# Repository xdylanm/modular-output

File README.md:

# Output Module

An audio output module for Eurorack, combining two mono input channels into a stereo output with a panning mixer. The stereo output is suitable to drive headphones or small speakers.

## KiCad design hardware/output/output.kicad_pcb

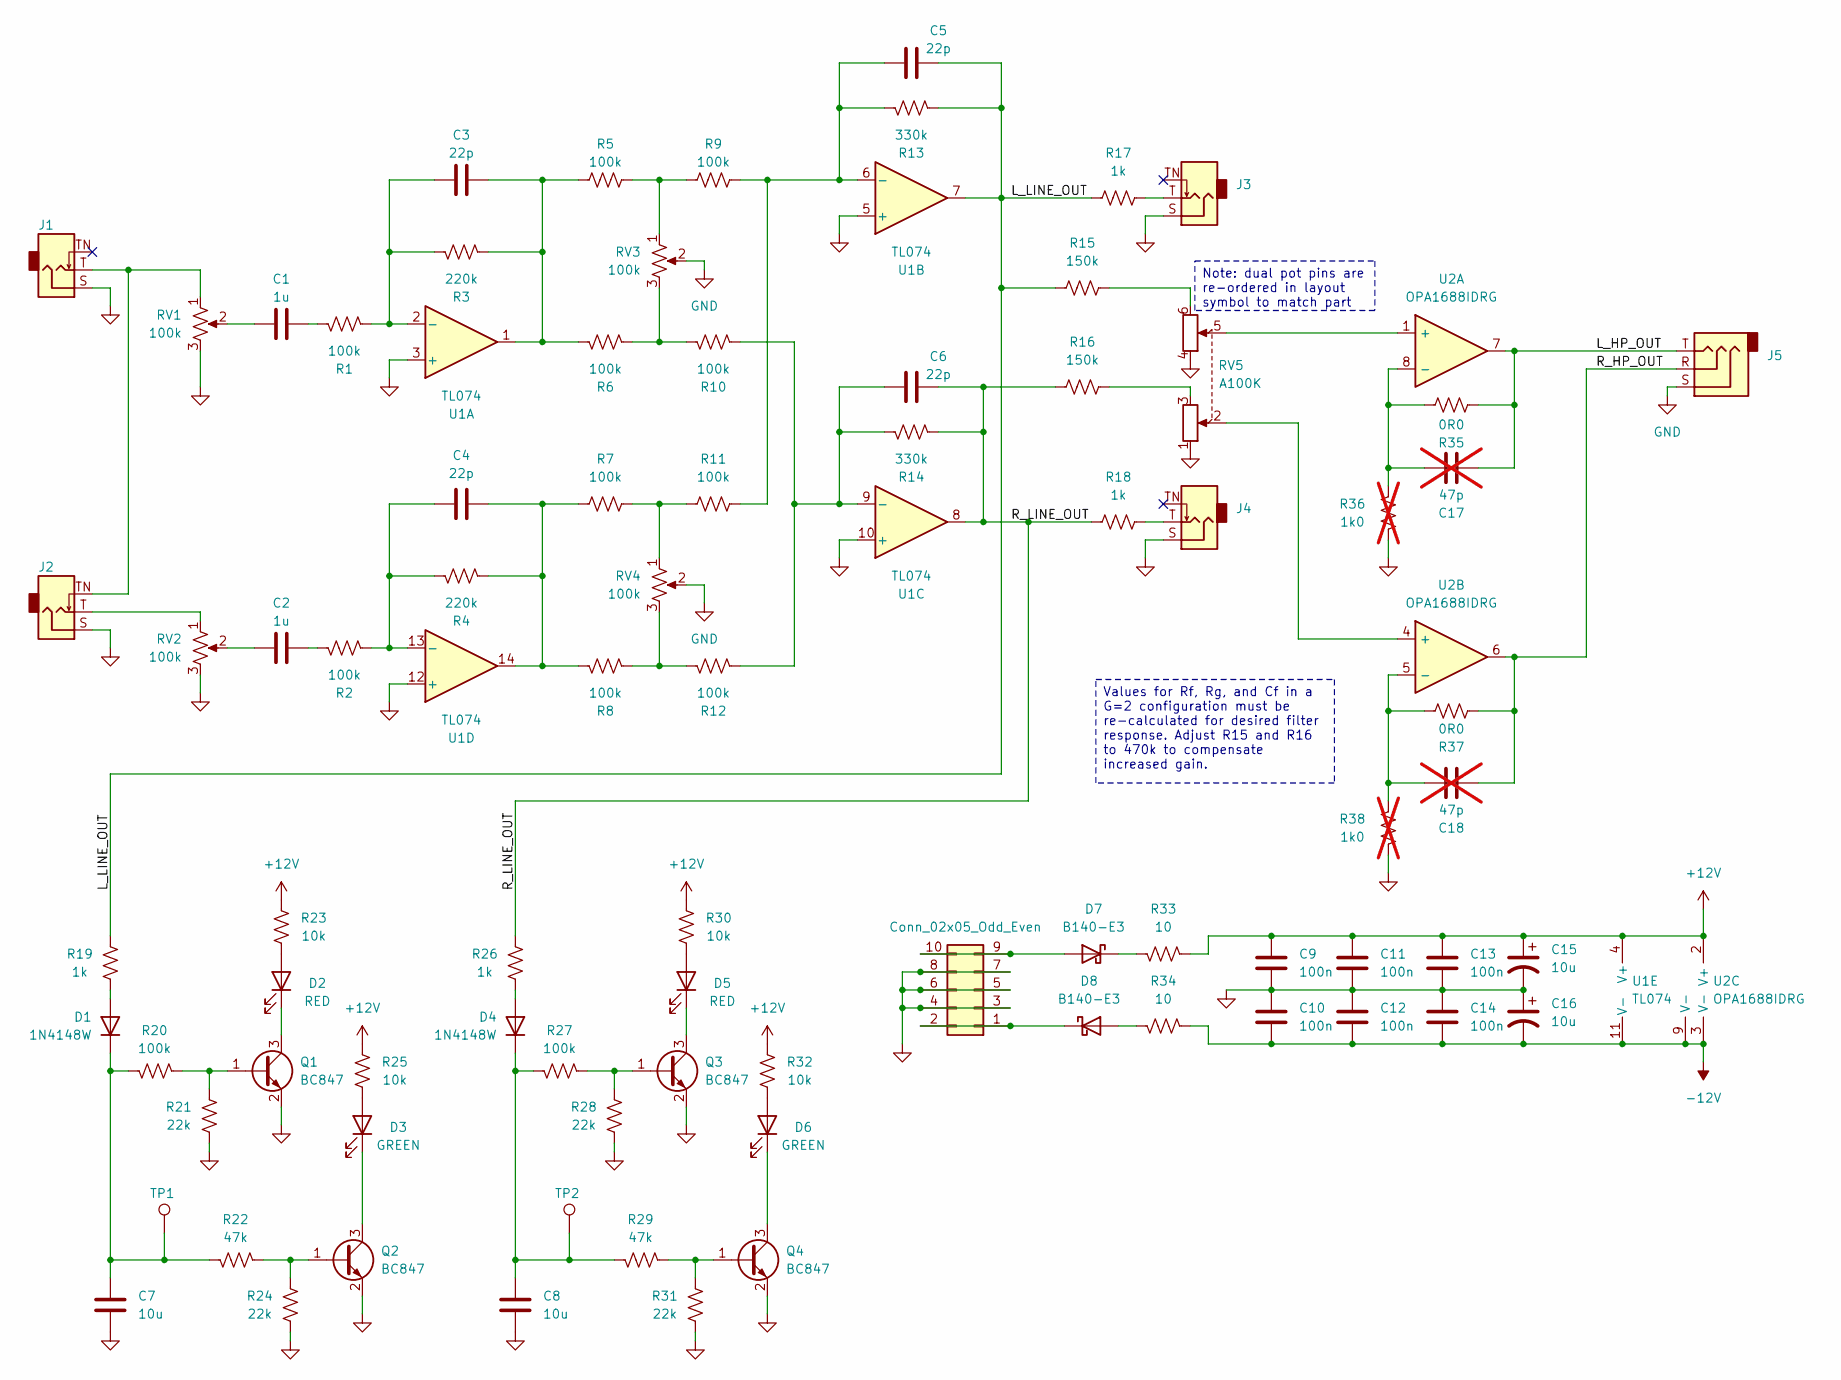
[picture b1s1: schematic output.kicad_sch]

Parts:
C1, C2: 1u; C_0805_2012Metric_Pad1.18x1.45mm_HandSolder
C3, C4, C5, C6: 22p; C_0805_2012Metric_Pad1.18x1.45mm_HandSolder
C7, C8: 10u; C_0805_2012Metric_Pad1.18x1.45mm_HandSolder
C9, C10, C11, C12, C13, C14: 100n; C_0805_2012Metric_Pad1.18x1.45mm_HandSolder
C15, C16: 10u; CP_Radial_D5.0mm_P2.00mm
C17, C18: 47p; C_0805_2012Metric_Pad1.18x1.45mm_HandSolder; not fitted
D1, D4: 1N4148W; D_SOD-123
D2, D5: RED; LED_D3.0mm_Clear
D3, D6: GREEN; LED_D3.0mm_Clear
D7, D8: B140-E3; D_SMA
J1, J2, J3, J4: AudioJack2_SwitchT; Jack_3.5mm_QingPu_WQP-PJ301M-12_Vertical_Slim
J5: AudioJack3; Jack_3.5mm_QingPu_WQP-PJ301CM_Vertical
J6: Conn_02x05_Odd_Even; IDC-Header_2x05_P2.54mm_Vertical
Q1, Q2, Q3, Q4: BC847; SOT-23
R1, R2, R5, R6, R7, R8, R9, R10, R11, R12, R20, R27: 100k; R_0805_2012Metric_Pad1.20x1.40mm_HandSolder
R3, R4: 220k; R_0805_2012Metric_Pad1.20x1.40mm_HandSolder
R13, R14: 330k; R_0805_2012Metric_Pad1.20x1.40mm_HandSolder
R15, R16: 150k; R_0805_2012Metric_Pad1.20x1.40mm_HandSolder
R17, R18, R19, R26: 1k; R_0805_2012Metric_Pad1.20x1.40mm_HandSolder
R21, R24, R28, R31: 22k; R_0805_2012Metric_Pad1.20x1.40mm_HandSolder
R22, R29: 47k; R_0805_2012Metric_Pad1.20x1.40mm_HandSolder
R23, R25, R30, R32: 10k; R_0805_2012Metric_Pad1.20x1.40mm_HandSolder
R33, R34: 10; R_0805_2012Metric_Pad1.20x1.40mm_HandSolder
R35, R37: 0R0; R_0805_2012Metric_Pad1.20x1.40mm_HandSolder
R36, R38: 1k0; R_0805_2012Metric_Pad1.20x1.40mm_HandSolder; not fitted
RV1, RV2, RV3, RV4: 100k; Potentiometer_Bourns_PTV09A-1_Single_Vertical
RV5: A100K; Potentiometer_Bourns_PTV112-4_Dual_Vertical
TP1, TP2: TestPoint; TestPoint_Pad_D1.5mm
U1: TL074; SOIC-14_3.9x8.7mm_P1.27mm
U2: OPA1688IDRG; WSON-8-1EP_3x3mm_P0.5mm_EP1.2x2mm

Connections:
+12V: C9.2, C11.2, C13.2, C15.1, R23.1, R25.1, R30.1, R32.1, R33.1, U1.4 (V+), U2.2 (V+)
-12V: C10.1, C12.1, C14.1, C16.2, R34.1, U1.11 (V-), U2.3 (V-), U2.9 (V-)
/L_HP_OUT: C17.2, J5.T, R35.1, U2.7
/L_LINE_OUT: C5.2, R13.2, R15.1, R17.1, R19.2, U1.7
/R_HP_OUT: C18.2, J5.R, R37.1, U2.6
/R_LINE_OUT: C6.2, R14.2, R16.1, R18.1, R26.2, U1.8
GND: C7.1, C8.1, C9.1, C10.2, C11.1, C12.2, C13.1, C14.2, C15.2, C16.1, J1.S, J2.S, J3.S, J4.S, J5.S, J6.3, J6.4, J6.5, J6.6, J6.7, J6.8, Q1.2 (E), Q2.2 (E), Q3.2 (E), Q4.2 (E), R21.1, R24.1, R28.1, R31.1, R36.2, R38.2, RV1.3, RV2.3, RV3.2, RV4.2, RV5.1, RV5.4, RV5.SH, U1.3 (+), U1.5 (+), U1.10 (+), U1.12 (+)
unnamed: C1.1, RV1.2
unnamed: C1.2, R1.1
unnamed: C2.1, RV2.2
unnamed: C2.2, R2.1
unnamed: C3.2, R3.2, R5.1, R6.1, U1.1
unnamed: C4.2, R4.2, R7.1, R8.1, U1.14
unnamed: D1.2 (A), R19.1
unnamed: C7.2, D1.1 (K), R20.2, R22.2, TP1.1
unnamed: D2.2 (A), R23.2
unnamed: D2.1 (K), Q1.3 (C)
unnamed: D3.2 (A), R25.2
unnamed: D3.1 (K), Q2.3 (C)
unnamed: D4.2 (A), R26.1
unnamed: C8.2, D4.1 (K), R27.2, R29.2, TP2.1
unnamed: D5.2 (A), R30.2
unnamed: D5.1 (K), Q3.3 (C)
unnamed: D6.2 (A), R32.2
unnamed: D6.1 (K), Q4.3 (C)
unnamed: D7.2 (A), J6.9, J6.10
unnamed: D7.1 (K), R33.2
unnamed: D8.2 (A), R34.2
unnamed: D8.1 (K), J6.1, J6.2
unnamed: J1.T, J2.TN, RV1.1
unnamed: J2.T, RV2.1
unnamed: J3.T, R17.2
unnamed: J4.T, R18.2
unnamed: Q1.1 (B), R20.1, R21.2
unnamed: Q2.1 (B), R22.1, R24.2
unnamed: Q3.1 (B), R27.1, R28.2
unnamed: Q4.1 (B), R29.1, R31.2
unnamed: R5.2, R9.1, RV3.1
unnamed: R6.2, R10.1, RV3.3
unnamed: R7.2, R11.1, RV4.1
unnamed: R8.2, R12.1, RV4.3
unnamed: R15.2, RV5.6
unnamed: R16.2, RV5.3
unnamed: C3.1, R1.2, R3.1, U1.2 (-)
unnamed: C5.1, R9.2, R11.2, R13.1, U1.6 (-)
unnamed: C6.1, R10.2, R12.2, R14.1, U1.9 (-)
unnamed: C4.1, R2.2, R4.1, U1.13 (-)
unnamed: RV5.5, U2.1 (+)
unnamed: C17.1, R35.2, R36.1, U2.8 (-)
unnamed: RV5.2, U2.4 (+)
unnamed: C18.1, R37.2, R38.1, U2.5 (-)

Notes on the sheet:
Note: dual pot pins are re-ordered in layout symbol to match part
Values for Rf, Rg, and Cf in a G=2 configuration must be re-calculated for desired filter response. Adjust R15 and R16 to 470k to compensate increased gain.

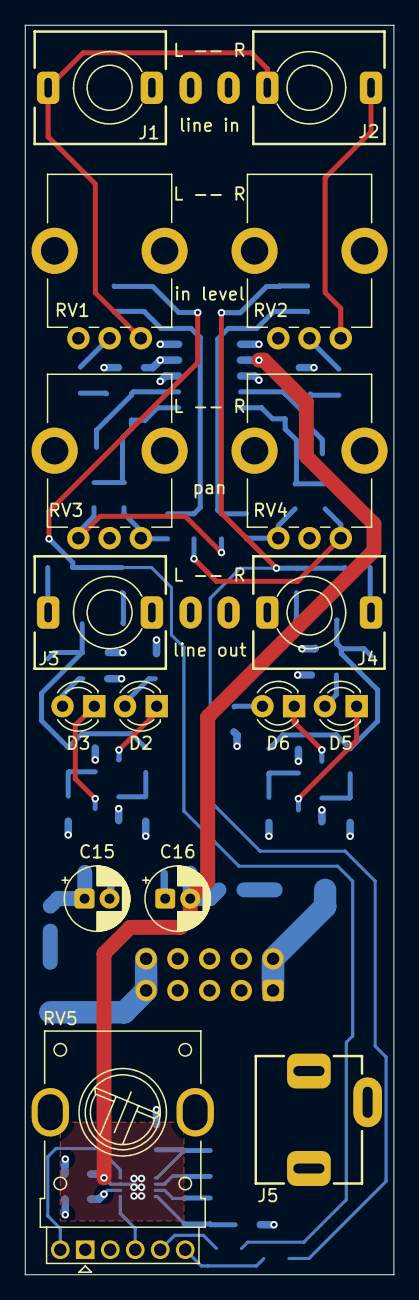
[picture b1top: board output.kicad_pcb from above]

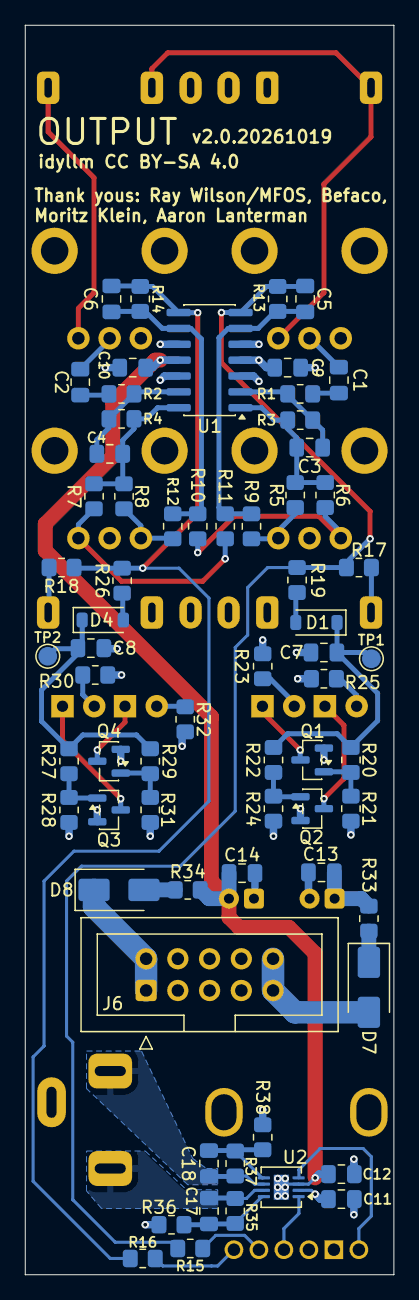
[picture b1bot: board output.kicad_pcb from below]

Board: 4 copper layers, 29.5 x 100.0 mm, 83 parts (67 on the bottom side), 51 nets.

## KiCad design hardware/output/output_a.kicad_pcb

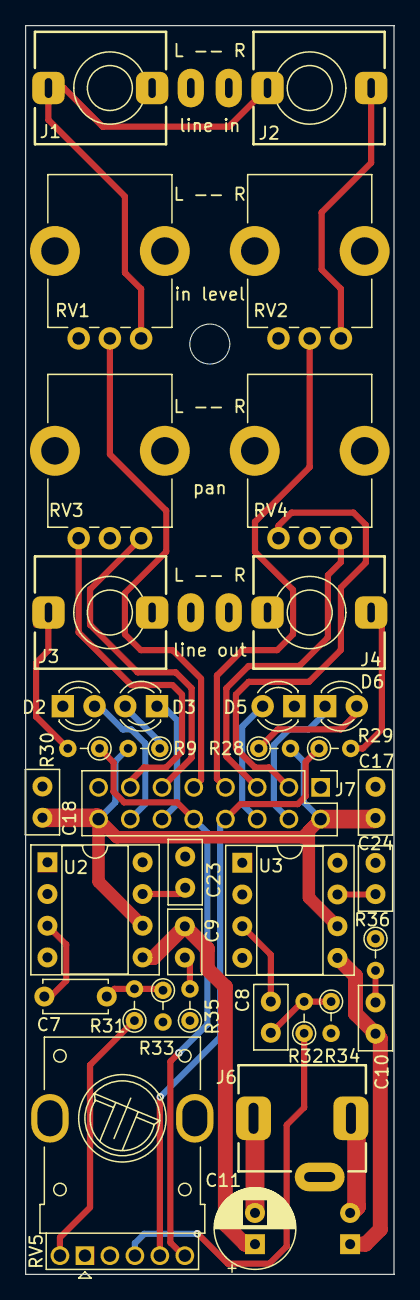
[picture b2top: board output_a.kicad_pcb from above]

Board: 2 copper layers, 29.5 x 100.0 mm, 38 parts (1 on the bottom side), 34 nets.

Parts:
C7: 1u; C_Disc_D5.0mm_W2.5mm_P5.00mm
C8: 1u; C_Disc_D5.0mm_W2.5mm_P2.50mm
C9, C10: 47n; C_Disc_D5.0mm_W2.5mm_P2.50mm
C11, C12: 220u; CP_Radial_D6.3mm_P2.50mm
C17, C18, C23, C24: 100n; C_Disc_D5.0mm_W2.5mm_P2.50mm
D2, D5: GREEN; LED_D3.0mm_Clear
D3, D6: RED; LED_D3.0mm_Clear
H1: MountingHole; MountingHole_3.2mm_M3_DIN965
J1, J2, J3, J4: AudioJack2_SwitchT; Jack_3.5mm_QingPu_WQP-PJ301M-12_Vertical
J6: AudioJack3; Jack_3.5mm_QingPu_WQP-PJ301CM_Vertical
J7: Conn_02x08_Odd_Even; PinHeader_2x08_P2.54mm_Vertical_ThinPad
R9, R28: 10k; R_Axial_DIN0204_L3.6mm_D1.6mm_P2.54mm_Vertical
R29, R30: 1k; R_Axial_DIN0204_L3.6mm_D1.6mm_P2.54mm_Vertical
R31, R32: 100k; R_Axial_DIN0204_L3.6mm_D1.6mm_P2.54mm_Vertical
R33, R34: 4k7; R_Axial_DIN0204_L3.6mm_D1.6mm_P2.54mm_Vertical
R35, R36: 10; R_Axial_DIN0204_L3.6mm_D1.6mm_P2.54mm_Vertical
RV1, RV2, RV3, RV4: 100k; Potentiometer_Bourns_PTV09A-1_Single_Vertical
RV5: A100K; Potentiometer_Bourns_PTV112-4_Dual_Vertical
U2, U3: LM386; DIP-8_W7.62mm_Socket

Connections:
+12V: C17.2, C18.2, J7.2, J7.16, R9.2, R28.2, U2.6 (V+), U3.6 (V+)
GND: C17.1, C18.1, C23.2, C24.2, D2.1 (K), D5.1 (K), J1.S, J2.S, J3.S, J4.S, J6.S, J7.1, J7.15, R33.2, R34.2, R35.1, R36.1, RV1.3, RV2.3, RV3.2, RV4.2, RV5.1, RV5.4, U2.2 (-), U2.4 (GND), U3.2 (-), U3.4 (GND)
L_LINE_IN_A: J7.9, RV1.2
L_LINE_OUT_A: J7.10, R30.1, RV5.3
L_LVL_G_LED_A: D2.2 (A), J7.14
L_LVL_R_LED_A: D3.1 (K), J7.12
L_PAN_1_A: J7.11, RV3.1
L_PAN_2_A: J7.13, RV3.3
unnamed: C7.2, R31.2, R33.1
unnamed: C8.2, R32.2, R34.1
unnamed: C9.2, R35.2
unnamed: C10.1, C12.1, U3.5
unnamed: C10.2, R36.2
unnamed: C9.1, C11.1, U2.5
unnamed: C11.2, J6.T
unnamed: C12.2, J6.R
unnamed: D3.2 (A), R9.1
unnamed: D6.2 (A), R28.1
unnamed: J1.T, J2.TN, RV1.1
unnamed: J2.T, RV2.1
unnamed: J3.T, R30.2
unnamed: J4.T, R29.2
unnamed: R31.1, RV5.2
unnamed: R32.1, RV5.5
unnamed: C7.1, U2.3 (+)
unnamed: C23.1, U2.7 (BYPASS)
unnamed: C8.1, U3.3 (+)
unnamed: C24.1, U3.7 (BYPASS)
R_LINE_IN_A: J7.7, RV2.2
R_LINE_OUT_A: J7.8, R29.1, RV5.6
R_LVL_G_LED_A: D5.2 (A), J7.6
R_LVL_R_LED_A: D6.1 (K), J7.4
R_PAN_1_A: J7.5, RV4.1
R_PAN_2_A: J7.3, RV4.3

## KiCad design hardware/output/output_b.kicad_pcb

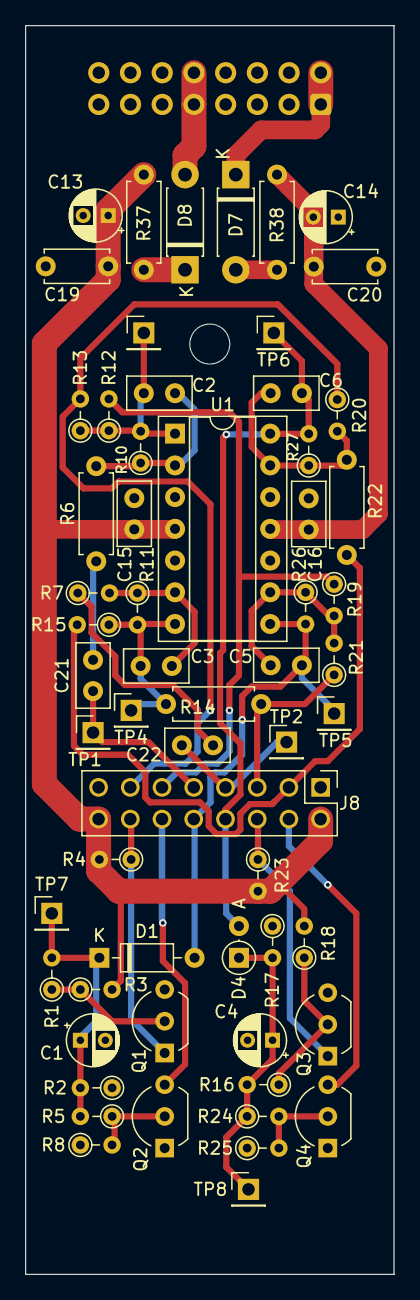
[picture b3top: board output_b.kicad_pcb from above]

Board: 2 copper layers, 29.5 x 100.0 mm, 62 parts (1 on the bottom side), 33 nets.

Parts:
C1, C4, C13, C14: 10u; CP_Radial_D4.0mm_P2.00mm
C2, C3, C5, C6: 22p; C_Disc_D5.0mm_W2.5mm_P2.50mm
C15, C16: 100n; C_Disc_D5.0mm_W2.5mm_P2.50mm
C19, C20: 100n; C_Disc_D5.0mm_W2.5mm_P5.00mm
C21, C22: 1u; C_Disc_D5.0mm_W2.5mm_P2.50mm
D1: 1N4148; D_DO-35_SOD27_P7.62mm_Horizontal
D4: 1N4148; D_DO-35_SOD27_P2.54mm_Vertical_AnodeUp
D7, D8: D_Schottky; D_DO-41_SOD81_P7.62mm_Horizontal
H2: MountingHole; MountingHole_3.2mm_M3_DIN965
J5: Conn_02x08_Odd_Even; IDC-Header_2x08_P2.54mm_Vertical
J8: Conn_02x08_Odd_Even; PinHeader_2x08_P2.54mm_Vertical_ThinPad
Q1, Q3: 2N3906; TO-92_Inline_Wide
Q2, Q4: 2N3904; TO-92_Inline_Wide
R1, R5, R7, R12, R13, R15, R16, R19, R20, R21, R24: 100k; R_Axial_DIN0204_L3.6mm_D1.6mm_P2.54mm_Vertical
R2, R17: 47k; R_Axial_DIN0204_L3.6mm_D1.6mm_P2.54mm_Vertical
R3, R18: 2M2; R_Axial_DIN0204_L3.6mm_D1.6mm_P2.54mm_Vertical
R4, R23: 10k; R_Axial_DIN0204_L3.6mm_D1.6mm_P2.54mm_Vertical
R6, R14, R22: 100k; R_Axial_DIN0207_L6.3mm_D2.5mm_P7.62mm_Horizontal
R8, R25: 15k; R_Axial_DIN0204_L3.6mm_D1.6mm_P2.54mm_Vertical
R10, R11: 220k; R_Axial_DIN0204_L3.6mm_D1.6mm_P2.54mm_Vertical
R26, R27: 330k; R_Axial_DIN0204_L3.6mm_D1.6mm_P2.54mm_Vertical
R37, R38: 10; R_Axial_DIN0207_L6.3mm_D2.5mm_P7.62mm_Horizontal
TP1, TP2, TP3, TP4, TP5, TP6, TP7, TP8: TestPoint; PinHeader_1x01_P2.54mm_Vertical
U1: TL074; DIP-14_W7.62mm_Socket

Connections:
+12V: C13.1, C15.2, C19.2, J8.2, J8.16, R3.2, R4.2, R18.2, R23.2, R37.1, U1.4 (V+)
-12V: C14.2, C16.1, C20.1, R38.1, U1.11 (V-)
GND: C1.2, C4.2, C13.2, C14.1, C15.1, C16.2, C19.1, C20.2, J5.3, J5.4, J5.5, J5.6, J5.7, J5.8, J8.1, J8.15, Q1.3 (C), Q2.1 (E), Q3.3 (C), Q4.1 (E), R2.1, R8.1, R17.1, R25.1, U1.3 (+), U1.5 (+), U1.10 (+), U1.12 (+)
L_LINE_IN_B: C21.1, J8.9, TP1.1
L_LINE_OUT_B: C5.2, D1.2 (A), J8.10, R26.2, TP5.1, U1.8
L_LVL_G_LED_B: J8.14, Q1.1 (E), R4.1
L_LVL_R_LED_B: J8.12, Q2.3 (C)
L_PAN_1_B: J8.11, R12.2, R19.1
L_PAN_2_B: J8.13, R13.2, R20.1
unnamed: C2.2, R10.2, R12.1, R13.1, TP3.1, U1.1
unnamed: C3.2, R11.2, R14.1, R15.1, TP4.1, U1.7
unnamed: C21.2, R6.1
unnamed: C22.2, R7.1
unnamed: C1.1, D1.1 (K), R1.2, R2.2, R5.2, TP7.1
unnamed: C4.1, D4.1 (K), R16.2, R17.2, R24.1, TP8.1
unnamed: D7.2 (A), R38.2
unnamed: D7.1 (K), J5.1, J5.2
unnamed: D8.2 (A), J5.9, J5.10
unnamed: D8.1 (K), R37.2
unnamed: Q1.2 (B), R1.1, R3.1
unnamed: Q2.2 (B), R5.1, R8.2
unnamed: Q3.2 (B), R16.1, R18.1
unnamed: Q4.2 (B), R24.2, R25.2
unnamed: C2.1, R6.2, R10.1, U1.2 (-)
unnamed: C3.1, R7.2, R11.1, U1.6 (-)
unnamed: C5.1, R19.2, R21.2, R26.1, U1.9 (-)
unnamed: C6.1, R20.2, R22.2, R27.1, U1.13 (-)
R_LINE_IN_B: C22.1, J8.7, TP2.1
R_LINE_OUT_B: C6.2, D4.2 (A), J8.8, R27.2, TP6.1, U1.14
R_LVL_G_LED_B: J8.6, Q3.1 (E), R23.1
R_LVL_R_LED_B: J8.4, Q4.3 (C)
R_PAN_1_B: J8.5, R14.2, R21.1
R_PAN_2_B: J8.3, R15.2, R22.1

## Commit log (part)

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2025-02-22 Copying the module over from the 'toolbox' and adding documentation
2025-10-03 Converted project to MkDocs/Material
2025-10-03 Fixed links, added schematic to nav bar

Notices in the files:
hardware/output/output.kicad_pcb:
CC BY-SA 4.0
idyllm CC BY-SA 4.0
